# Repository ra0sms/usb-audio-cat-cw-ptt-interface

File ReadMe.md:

## USB AUDIO CAT PTT CW interface for any transceiver

One USB connection - two USB devices. 

USB Audio Codec and COM-port for CAT CW and PTT. Based on CH334R (usb-hub), CH340C (usb-com) and CM108B (usb audio).

More information - https://ra0sms.com/usb-audio-cat-interface/

-------------------------------------------

PCB dimension: 80*48 mm

[Gerber files](KiCad/usb_audio_cat/usb_audio_cat_gerbers.zip)

[Schematic](KiCad/usb_audio_cat/usb_audio_cat.pdf)

Recommended enclosure - 80-50-20 mm (https://aliexpress.ru/item/1005006828585850.html)

### PCB

### Boxed version

### Schematic

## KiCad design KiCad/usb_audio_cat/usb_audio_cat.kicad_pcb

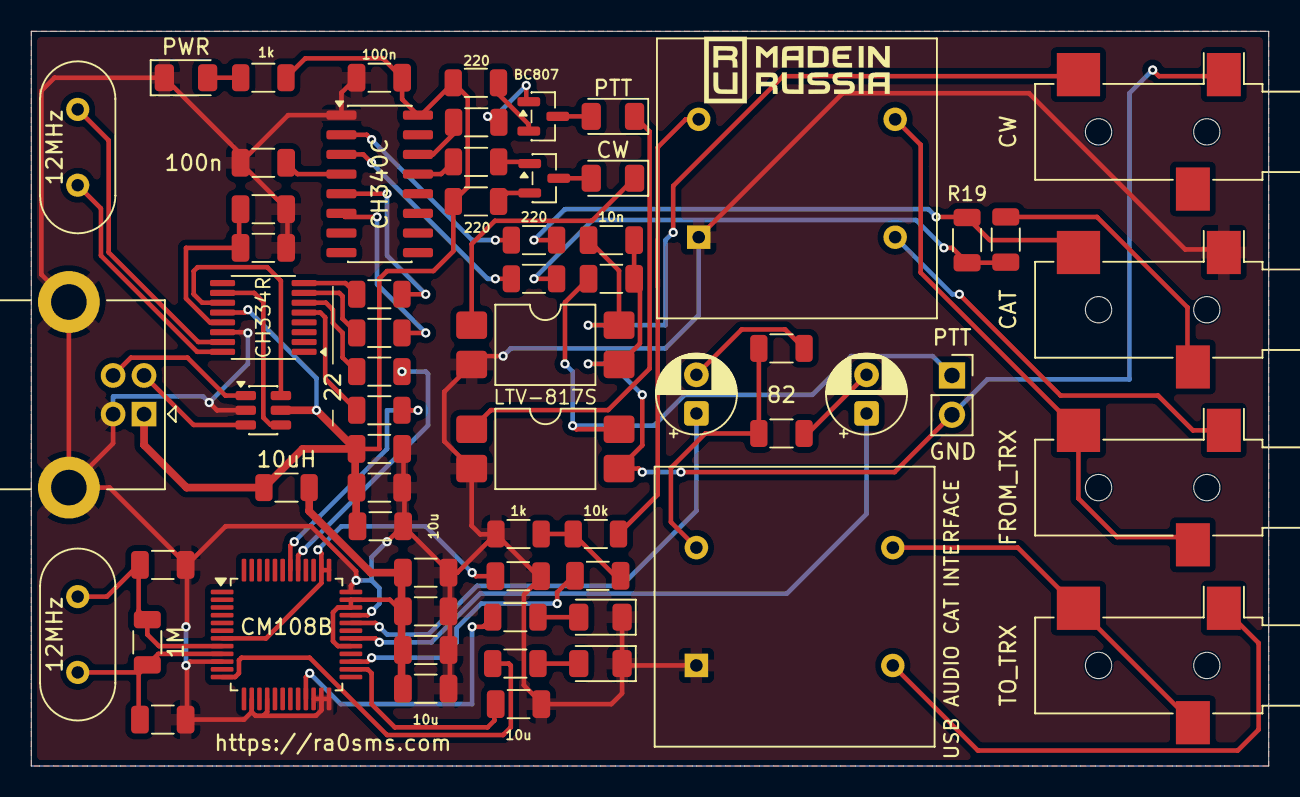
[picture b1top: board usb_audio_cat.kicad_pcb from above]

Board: 2 copper layers, 80.0 x 47.5 mm, 64 parts (0 on the bottom side), 58 nets.

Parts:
C1, C3: 22; C_1206_3216Metric
C2, C7, C10, C11, C17, C18: 100n; C_1206_3216Metric
C4, C19, C20: 10n; C_1206_3216Metric
C5, C6, C8, C9, C12, C13, C14: 10u; C_1206_3216Metric
C15, C16: 470uF; CP_Radial_D5.0mm_P2.50mm
D1: PWR; LED_1206_3216Metric
D2: OUT; LED_1206_3216Metric
D3: IN; LED_1206_3216Metric
D4: PTT; LED_1206_3216Metric
D5: CW; LED_1206_3216Metric
J1: USB_B; USB_B_Lumberg_2411_02_Horizontal
J2: TO_TRX; Jack_3.5mm_CUI_SJ-3523-SMT_Horizontal
J3: FROM_TRX; Jack_3.5mm_CUI_SJ-3523-SMT_Horizontal
J4: CAT; Jack_3.5mm_CUI_SJ-3523-SMT_Horizontal
J5: CW; Jack_3.5mm_CUI_SJ-3523-SMT_Horizontal
J6: PTT; PinSocket_1x02_P2.54mm_Vertical
L1: 10uH; R_1206_3216Metric
Q1, Q2: BC807; SOT-23
R1, R7, R15, R16: 1k; R_1206_3216Metric
R2: 1M; R_1206_3216Metric
R3, R6: 470; R_1206_3216Metric
R4, R5, R11, R12: 22; R_1206_3216Metric
R8: 10k; R_1206_3216Metric
R9, R10: 82; R_1206_3216Metric
R13, R14, R17, R18: 220; R_1206_3216Metric
R19, R20: 0; R_1206_3216Metric
T1, T2: 600:600; Transformer_NF_ETAL_1-1_P1200
U1: USBLC6; SOT-23-6
U2: CM108B; LQFP-48_7x7mm_P0.5mm
U3: CH334R; QSOP-16_3.9x4.9mm_P0.635mm
U4: CH340C; SOIC-16_3.9x9.9mm_P1.27mm
U5, U6: LTV-817S; SMDIP-4_W9.53mm
Y1, Y2: 12MHz; Crystal_HC18-U_Vertical

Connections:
+5V: C2.1, C4.1, C5.1, C17.1, J1.1 (VBUS), L1.2, R1.2, R17.2, R18.2, U1.5 (VBUS), U3.12 (V5), U4.16 (VCC)
DM1: R12.1, U3.7 (DM1-)
DM2: R4.2, U3.5 (DM2-)
DP1: R11.1, U3.8 (DP1+)
DP2: R5.2, U3.6 (DP2+)
GND: C1.1, C2.2, C3.1, C4.2, C5.2, C6.1, C7.1, C8.2, C9.1, C10.2, C11.2, C12.2, C13.2, C17.2, C18.1, D1.1 (K), D2.1 (K), D3.1 (K), J1.4 (GND), J1.5 (Shield), J4.S, R7.1, T1.1 (AA), T2.1 (AA), U1.2 (GND), U2.10, U2.14, U2.16, U2.22, U2.23, U2.24, U2.33, U2.36, U3.14 (GND), U4.1 (GND), U5.2, U6.2
GNDREF: C19.2, C20.2, J5.S, J6.2, U5.3, U6.3
unnamed: C1.2, R2.2, U2.8, Y1.2
unnamed: C3.2, R2.1, U2.9, Y1.1
unnamed: C8.1, U2.7, U2.37, U2.38
unnamed: C9.2, U2.26
unnamed: C10.1, C11.1, C12.1, C13.1, L1.1, U2.29, U2.34, U2.35
unnamed: C14.1, U2.27
unnamed: C14.2, R7.2, R8.2
unnamed: C15.1, U2.32
unnamed: C15.2, R9.1
unnamed: C16.1, U2.30
unnamed: C16.2, R10.1
unnamed: C19.1, J5.T, U5.4
unnamed: D1.2 (A), R1.1
unnamed: D2.2 (A), R3.1
unnamed: D3.2 (A), R6.1
unnamed: D4.2 (A), Q1.3 (C)
unnamed: D4.1 (K), U6.1
unnamed: D5.2 (A), Q2.3 (C)
unnamed: D5.1 (K), U5.1
unnamed: J1.3 (D+), U1.1 (I/O1)
unnamed: J1.2 (D-), U1.3 (I/O2)
unnamed: J4.R, R20.2
unnamed: C20.1, J6.1, U6.4
unnamed: Q1.1 (B), R15.1
unnamed: Q1.2 (E), R17.1
unnamed: Q2.1 (B), R16.1
unnamed: Q2.2 (E), R18.1
unnamed: R3.2, U2.12
unnamed: R4.1, U2.42
unnamed: R5.1, U2.41
unnamed: R6.2, U2.21
unnamed: R9.2, R10.2, T1.3 (AB)
unnamed: J2.R, J2.T, T1.4 (SA)
unnamed: J2.S, T1.6 (SB)
unnamed: R8.1, T2.3 (AB)
unnamed: J3.R, J3.T, T2.4 (SA)
unnamed: J3.S, T2.6 (SB)
unnamed: U1.4 (I/O2), U3.10 (DMU-)
unnamed: U1.6 (I/O1), U3.11 (DPU+)
unnamed: C6.2, C7.2, U3.13 (VDD33_{LDO})
unnamed: U3.16 (XI), Y2.1
unnamed: U3.15 (XO), Y2.2
unnamed: R14.1, U4.3 (RXD)
unnamed: R13.1, U4.2 (TXD)
unnamed: R11.2, U4.5 (UD+)
unnamed: R12.2, U4.6 (UD-)
unnamed: C18.2, U4.4 (V3)
unnamed: R16.2, U4.13 (~DTR)
unnamed: R15.2, U4.14 (~RTS)
RXD: R14.2, R19.2, R20.1
TXD: J4.T, R13.2, R19.1

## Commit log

2026-05-18 add ReadMe
